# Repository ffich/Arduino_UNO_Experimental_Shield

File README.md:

# Arduino_UNO_Experimental_Shield
Experimental shield for Arduino UNO form factor boards.

Welcome to the official repository of the **UNO Experimental SHIELD**, an expansion board designed to provide a complete laboratory environment for experimenting, testing, and learning with the Arduino UNO Boards (e.g **UNO Q**).
This shield integrates digital and analog I/O, SPI, I2C, sensors, memory, and diagnostics to create a versatile platform ideal for rapid prototyping, debugging, and education.

---

## 🚀 Key Features

### 🔹 Digital I/O
- SMD LEDs on pins **D2, D3, D6, D7, D8, D9**
- Push buttons on pins **A2, A3**

### 🔹 Analog Inputs
- **Two 100 kΩ trimmers** on analog inputs **A0, A1**  

### 🔹 Serial Communication
- **USB-to-Serial bridge** (CH340)  

### 🔹 CAN Bus
- **CAN transceiver** (TJA1051T3)  
- **120 Ω termination resistor** enabled by jumper  
- Screw terminal output: CANH / CANL

### 🔹 RS-485
- **RS485 transceiver**
- **120 Ω termination resistor** enabled by jumper  
- Screw terminal output: A / B 

### 🔹 I2C Display
- Integrated **SSD1306 OLED display**

### 🔹 I2C Thermometer
- Integrated **TMP102 thermo**  

### 🔹 SPI Memory
- **25LC256 EEPROM** connected to hardware SPI  
- Dedicated Chip Select line

### 🔹 Crypto Chip
- Integrated **ATECC608C**  - 

---

## 📐 Pinout Summary

### Digital I/O
| UNO Pin | Shield Function |
|------------|-----------------|
| D2, D3, D6, D7, D8, D9 | LED  |
| A2, A3 | Buttons  |

### Analog
| Pin | Function |
|-----|----------|
| A0 | Trimmer 1 |
| A1 | Trimmer 2 |

### Peripherals
| Function | Pin |
|----------|-----|
| SPI EEPROM | MOSI / MISO / SCK + CS |
| I2C OLED | SDA / SCL |
| I2C Thermo | SDA / SCL |
| I2C Crypto Chip | SDA / SCL |
| CAN | CAN_TX / CAN_RX |
| RS485 | TX / RX |
| USB-Serial | TX / RX |

The Shield is compatible with both Arduino UNOs with 3V3 and 5V logic (some jumpers allow to adapt the voltage levels).

---

## 🛠️ Project Goals

This shield is intended for:
- Users who want a **complete test environment** for Arduino UNO Boards (e.g. **UNO Q**, **UNO R4**) 
- Makers performing **rapid firmware debugging**  
- Schools, workshops, and educational labs  
- Testing all core firmware interfaces (PWM, ADC, SPI, I2C, CAN, UART)

---

## 📷 Logo

The official project logo is available in the `/assets/logo/` directory.

---

## 📝 License

This project is released under the **MIT License**, unless otherwise specified for hardware files.

---

## 🤝 Contributing

Pull requests and issues are welcome!  
Contributions improving documentation, firmware examples, or hardware design are highly appreciated.

---

## 📫 Contact

For questions or suggestions, open an Issue in the repository or contact the maintainer.

---

Happy experimenting! 🔧✨

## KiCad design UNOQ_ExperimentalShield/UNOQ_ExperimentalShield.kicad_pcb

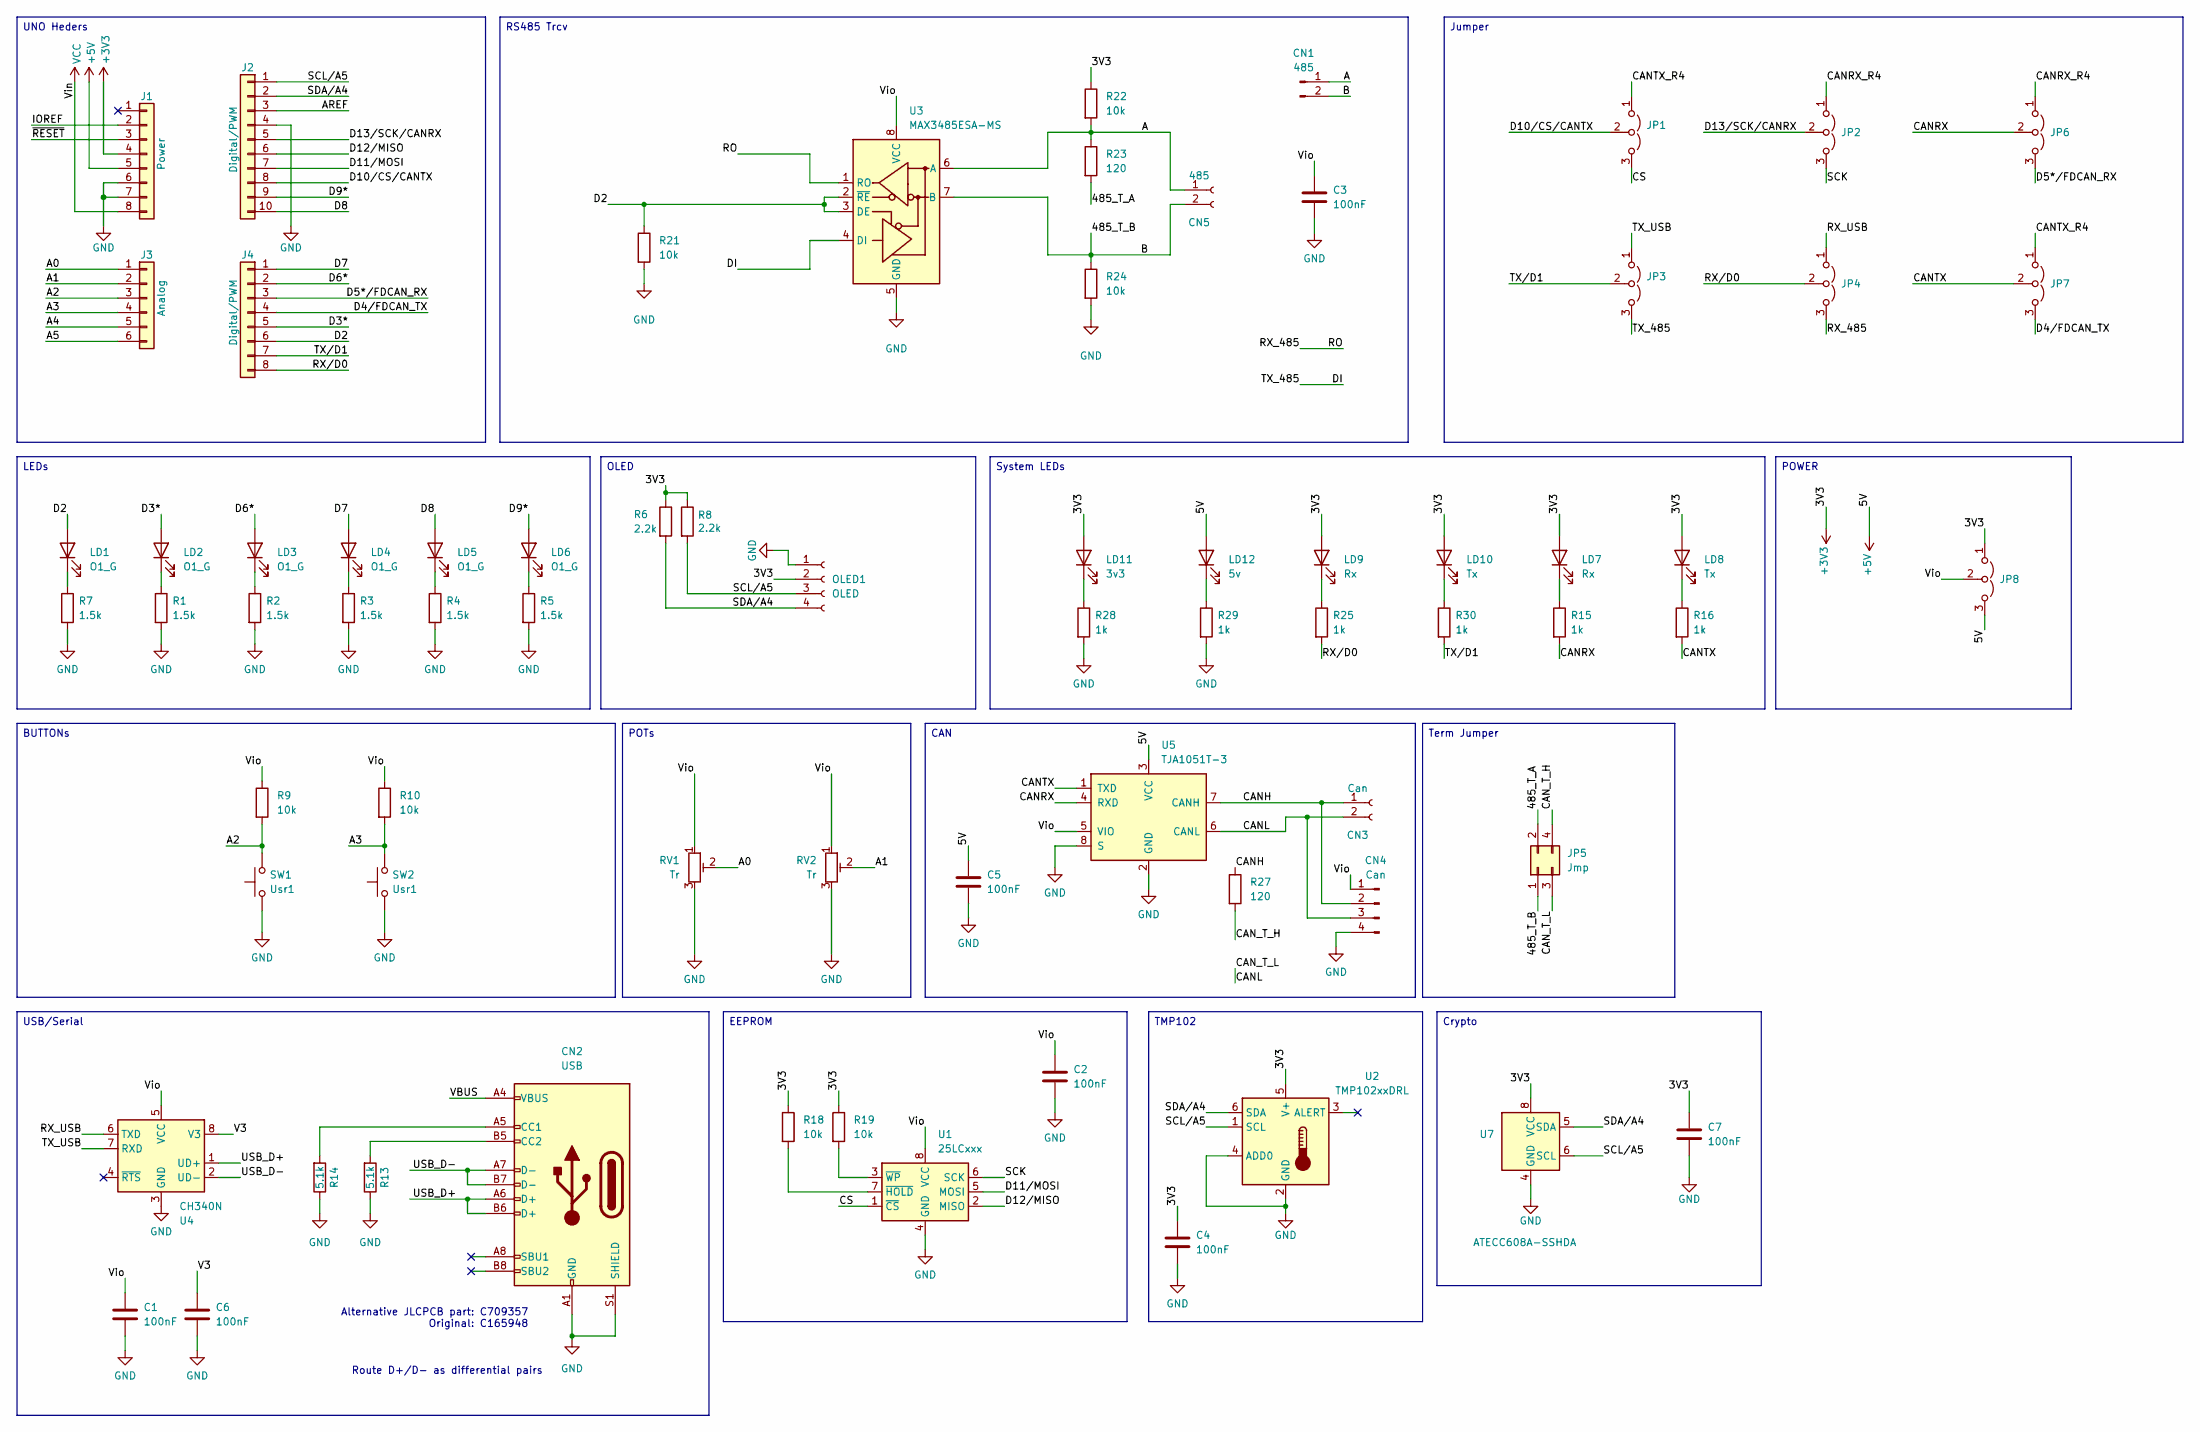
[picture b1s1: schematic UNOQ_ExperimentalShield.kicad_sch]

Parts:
C1, C2, C3, C4, C5, C6, C7: 100nF; C_0402_1005Metric; LCSC C155422
CN1: 485; PinHeader_1x02_P2.54mm_Vertical; LCSC C5360898
CN2: USB; USB_C_Receptacle_HRO_TYPE-C-31-M-12; LCSC C165948
CN3: Can; TerminalBlock_Phoenix_MPT-0,5-2-2.54_1x02_P2.54mm_Horizontal; LCSC C474920
CN4: Can; PinHeader_1x04_P2.54mm_Vertical; LCSC C2905435
CN5: 485; TerminalBlock_Phoenix_MPT-0,5-2-2.54_1x02_P2.54mm_Horizontal; LCSC C474920
J1: Power; PinHeader_1x08_P2.54mm_Vertical; LCSC C32713274
J2: Digital/PWM; PinHeader_1x10_P2.54mm_Vertical; LCSC C57369
J3: Analog; PinHeader_1x06_P2.54mm_Vertical; LCSC C32713272
J4: Digital/PWM; PinHeader_1x08_P2.54mm_Vertical; LCSC C32713274
JP1, JP2, JP3, JP4, JP6, JP7, JP8: Jmp; PinHeader_1x03_P2.54mm_Vertical; LCSC C49257
JP5: Jmp; PinHeader_2x02_P2.54mm_Vertical; LCSC C32713275
LD1, LD2, LD3, LD4, LD5, LD6: O1_G; LED_0603_1608Metric; LCSC C12624
LD7, LD9: Rx; LED_0603_1608Metric; LCSC C2286
LD8, LD10: Tx; LED_0603_1608Metric; LCSC C2286
LD11: 3v3; LED_0603_1608Metric; LCSC C2286
LD12: 5v; LED_0603_1608Metric; LCSC C2286
OLED1: OLED; OLED096; LCSC C5248080
R1, R2, R3, R4, R5, R7: 1.5k; R_0402_1005Metric; LCSC C25867
R6, R8: 2.2k; R_0603_1608Metric
R9, R10, R18, R19, R21, R22, R24: 10k; R_0402_1005Metric; LCSC C174175
R13, R14: 5.1k; R_0402_1005Metric; LCSC C25905
R15, R16, R25, R28, R29, R30: 1k; R_0402_1005Metric; LCSC C140196
R23, R27: 120; R_0603_1608Metric; LCSC C177328
RV1, RV2: Tr; Potentiometer_Bourns_3386P_Vertical; LCSC C116303
SW1, SW2: Usr1; SW_SPST_PTS810; LCSC C221895
U1: 25LCxxx; SO-8_3.9x4.9mm_P1.27mm; LCSC C84670
U2: TMP102xxDRL; SOT-563; LCSC C99269
U3: MAX3485ESA-MS; SOIC-8_3.9x4.9mm_P1.27mm; LCSC C7434431
U4: CH340N; JEITA_SOIC-8_3.9x4.9mm_P1.27mm; LCSC C2977777
U5: TJA1051T-3; SOIC-8_3.9x4.9mm_P1.27mm; LCSC C38695
U7: ATECC608A-SSHDA; SOIC-8_3.9x4.9mm_P1.27mm; LCSC C28975195

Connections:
+3V3: C4.1, C7.1, J1.4, JP8.1 (A), LD7.2 (A), LD8.2 (A), LD9.2 (A), LD10.2 (A), LD11.2 (A), OLED1.2, R6.1, R8.1, R18.1, R19.1, R22.1, U2.5 (V+), U7.8 (VCC)
+5V: C5.1, J1.5, JP8.3 (B), LD12.2 (A), U5.3 (VCC)
/485_T_A: JP5.2, R23.2
/485_T_B: CN1.2, CN5.2, JP5.1, R24.1, U3.7 (B)
/A: CN1.1, CN5.1, R22.2, R23.1, U3.6 (A)
/A0: J3.1, RV1.2
/A1: J3.2, RV2.2
/A2: J3.3, R9.2, SW1.2
/A3: J3.4, R10.2, SW2.2
/A4: J3.5
/A5: J3.6
/AREF: J2.3
/CANH: CN3.1, CN4.2, R27.1, U5.7 (CANH)
/CANL: CN3.2, CN4.3, JP5.3, U5.6 (CANL)
/CANRX: JP6.2 (C), R15.2, U5.4 (RXD)
/CANRX_R4: JP2.1 (A), JP6.1 (A)
/CANTX: JP7.2 (C), R16.2, U5.1 (TXD)
/CANTX_R4: JP1.1 (A), JP7.1 (A)
/CAN_T_H: JP5.4, R27.2
/CS: JP1.3 (B), U1.1 (~CS)
/D2: J4.6, LD1.2 (A), R21.1, U3.2 (~RE), U3.3 (DE)
/D3*: J4.5, LD2.2 (A)
/D4/FDCAN_TX: J4.4, JP7.3 (B)
/D5*/FDCAN_RX: J4.3, JP6.3 (B)
/D6*: J4.2, LD3.2 (A)
/D7: J4.1, LD4.2 (A)
/D8: J2.10, LD5.2 (A)
/D9*: J2.9, LD6.2 (A)
/D10/CS/CANTX: J2.8, JP1.2 (C)
/D11/MOSI: J2.7, U1.5 (MOSI)
/D12/MISO: J2.6, U1.2 (MISO)
/D13/SCK/CANRX: J2.5, JP2.2 (C)
/DI: JP3.3 (B), U3.4 (DI)
/IOREF: J1.2
/RO: JP4.3 (B), U3.1 (RO)
/RX_USB: JP4.1 (A), U4.6 (TXD)
/RX/D0: J4.8, JP4.2 (C), R25.2
/SCK: JP2.3 (B), U1.6 (SCK)
/SCL/A5: J2.1, OLED1.3, R8.2, U2.1 (SCL), U7.6 (SCL)
/SDA/A4: J2.2, OLED1.4, R6.2, U2.6 (SDA), U7.5 (SDA)
/TX_USB: JP3.1 (A), U4.7 (RXD)
/TX/D1: J4.7, JP3.2 (C), R30.2
/USB_D+: CN2.A6 (D+), CN2.B6 (D+), U4.1 (UD+)
/USB_D-: CN2.A7 (D-), CN2.B7 (D-), U4.2 (UD-)
/V3: C6.1, U4.8 (V3)
/VBUS: CN2.A4 (VBUS), CN2.A9 (VBUS), CN2.B4 (VBUS), CN2.B9 (VBUS)
/Vio: C1.1, C2.1, C3.1, CN4.1, JP8.2 (C), R9.1, R10.1, RV1.1, RV2.1, U1.8 (VCC), U3.8 (VCC), U4.5 (VCC), U5.5 (VIO)
/~RESET: J1.3
GND: C1.2, C2.2, C3.2, C4.2, C5.2, C6.2, C7.2, CN2.A1 (GND), CN2.A12 (GND), CN2.B1 (GND), CN2.B12 (GND), CN2.S1 (SHIELD), CN4.4, J1.6, J1.7, J2.4, OLED1.1, R1.2, R2.2, R3.2, R4.2, R5.2, R7.2, R13.1, R14.1, R21.2, R24.2, R28.2, R29.2, RV1.3, RV2.3, SW1.1, SW2.1, U1.4 (GND), U2.2 (GND), U2.4 (ADD0), U3.5 (GND), U4.3 (GND), U5.2 (GND), U5.8 (S), U7.4 (GND)
unnamed: CN2.A5 (CC1), R14.2
unnamed: CN2.B5 (CC2), R13.2
unnamed: LD1.1 (K), R7.1
unnamed: LD2.1 (K), R1.1
unnamed: LD3.1 (K), R2.1
unnamed: LD4.1 (K), R3.1
unnamed: LD5.1 (K), R4.1
unnamed: LD6.1 (K), R5.1
unnamed: LD7.1 (K), R15.1
unnamed: LD8.1 (K), R16.1
unnamed: LD9.1 (K), R25.1
unnamed: LD10.1 (K), R30.1
unnamed: LD11.1 (K), R28.1
unnamed: LD12.1 (K), R29.1
unnamed: R18.2, U1.7 (~HOLD)
unnamed: R19.2, U1.3 (~WP)
VCC: J1.8

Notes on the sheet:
Route D+/D- as differential pairs
Alternative JLCPCB part: C709357 Original: C165948
System LEDs
LEDs
TMP102
Term Jumper
CAN
OLED
EEPROM
Crypto
RS485 Trcv
Jumper
POTs
POWER
UNO Heders
USB/Serial
BUTTONs

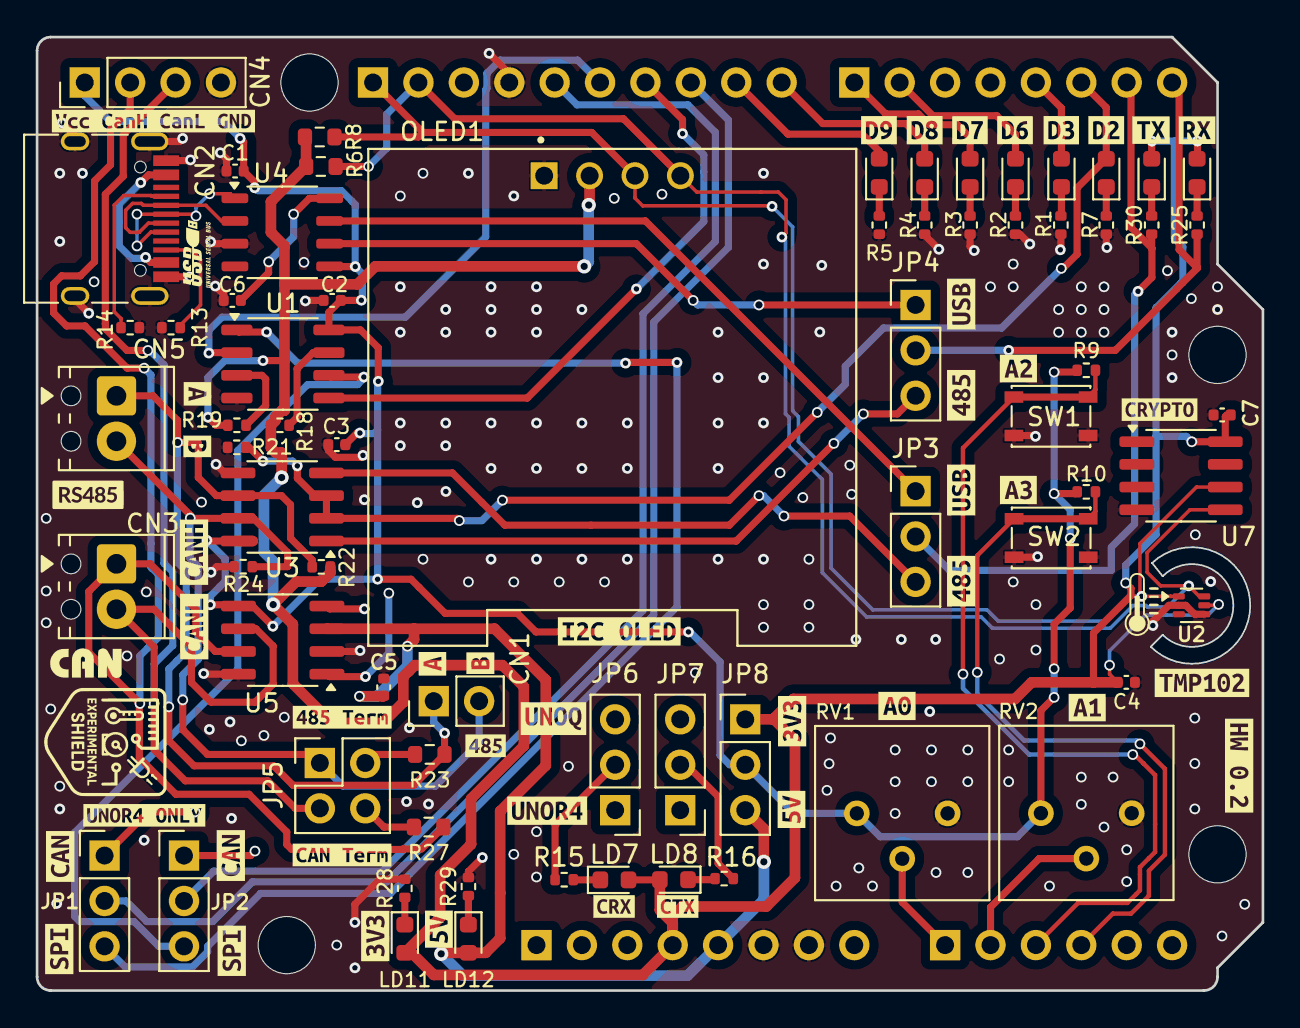
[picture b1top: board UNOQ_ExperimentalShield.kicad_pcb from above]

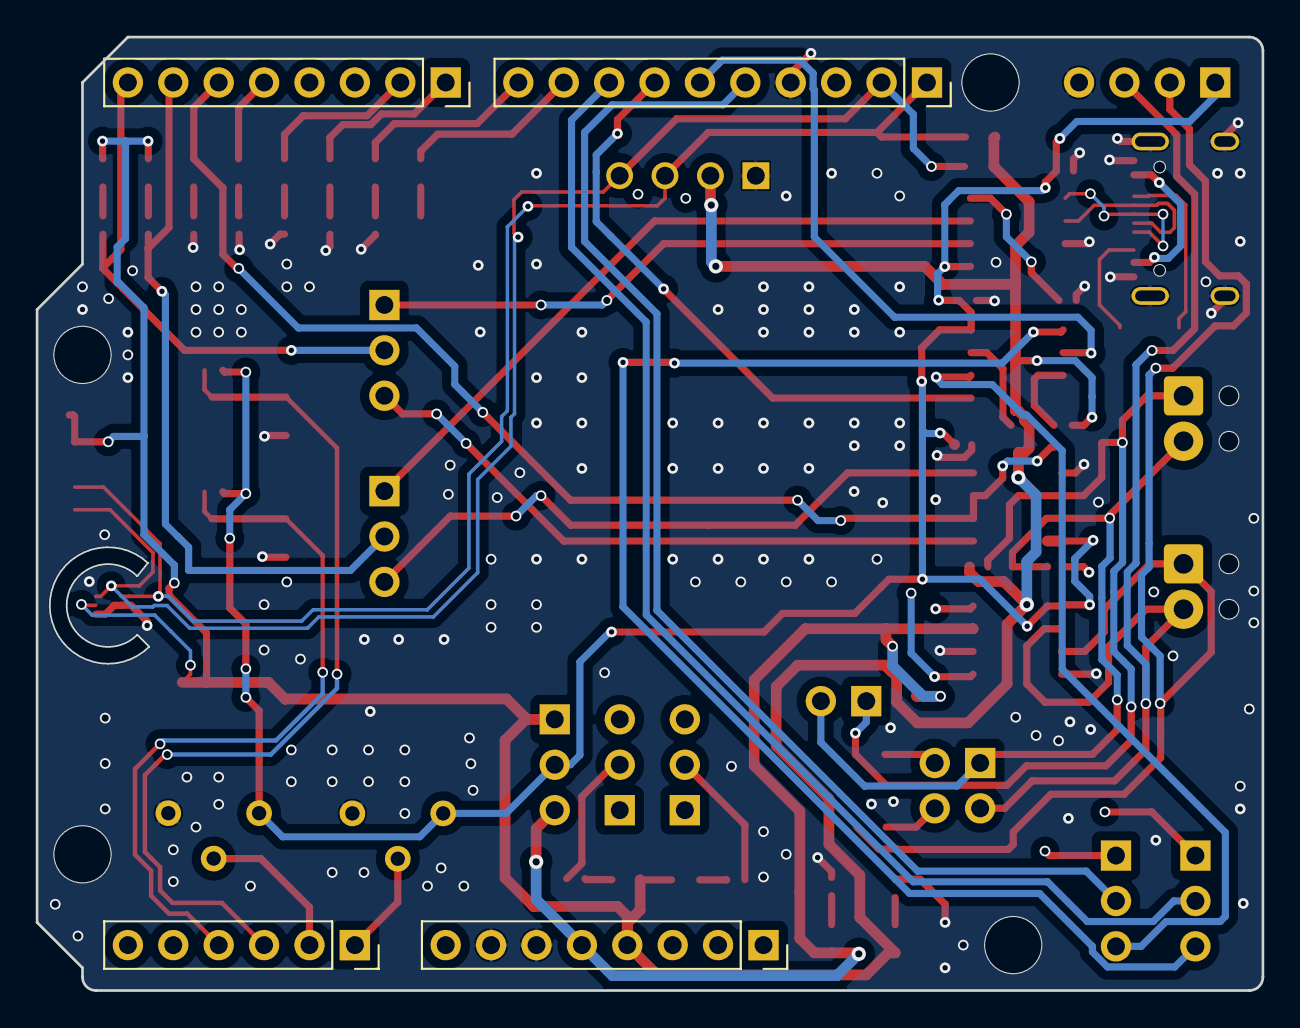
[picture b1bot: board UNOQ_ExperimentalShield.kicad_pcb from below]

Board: 4 copper layers, 68.6 x 53.3 mm, 119 parts (4 on the bottom side), 60 nets.

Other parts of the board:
MH1, MH2, MH3, MH4: MountingHole_3.2mm
kibuzzard-69DFD334: G***; kibuzzard-69DFD334
kibuzzard-69E2216E: G***; kibuzzard-69E2216E
kibuzzard-69E22173: G***; kibuzzard-69E22173
kibuzzard-69E66319: G***; kibuzzard-69E66319
kibuzzard-69ECB5A8: G***; kibuzzard-69ECB5A8
kibuzzard-69ECB57B: G***; kibuzzard-69ECB57B
kibuzzard-69ECB59B: G***; kibuzzard-69ECB59B
kibuzzard-69ECB574: G***; kibuzzard-69ECB574
kibuzzard-693AADEF: G***; kibuzzard-693AADEF
kibuzzard-697C8D0C: G***; kibuzzard-697C8D0C
kibuzzard-697C8D01: G***; kibuzzard-697C8D01
kibuzzard-697C896A: G***; kibuzzard-697C896A
kibuzzard-697C897C: G***; kibuzzard-697C897C
kibuzzard-697C8970: G***; kibuzzard-697C8970
kibuzzard-697C8977: G***; kibuzzard-697C8977
kibuzzard-69443E7E: G***; kibuzzard-69443E7E
kibuzzard-69443E38: G***; kibuzzard-69443E38
kibuzzard-69443E67: G***; kibuzzard-69443E67
kibuzzard-69595BB4: G***; kibuzzard-69595BB4
kibuzzard-69595BC0: G***; kibuzzard-69595BC0
kibuzzard-69595C5E: G***; kibuzzard-69595C5E
kibuzzard-69595C8D: G***; kibuzzard-69595C8D
kibuzzard-69595C64: G***; kibuzzard-69595C64
kibuzzard-69595C77: G***; kibuzzard-69595C77
kibuzzard-69595C82: G***; kibuzzard-69595C82
kibuzzard-69595C87: G***; kibuzzard-69595C87
kibuzzard-69595C92: G***; kibuzzard-69595C92
kibuzzard-69595C98: G***; kibuzzard-69595C98
kibuzzard-69595CA1: G***; kibuzzard-69595CA1
kibuzzard-69595CF0: G***; kibuzzard-69595CF0
kibuzzard-69595CF5: G***; kibuzzard-69595CF5
kibuzzard-69595D7B: G***; kibuzzard-69595D7B
kibuzzard-69595D77: G***; kibuzzard-69595D77
kibuzzard-69595D81: G***; kibuzzard-69595D81
kibuzzard-69764F79: G***; kibuzzard-69764F79
kibuzzard-69878B44: G***; kibuzzard-69878B44
kibuzzard-698784C3: G***; kibuzzard-698784C3
kibuzzard-698784D4: G***; kibuzzard-698784D4
kibuzzard-6976550D: G***; kibuzzard-6976550D
kibuzzard-6987886F: G***; kibuzzard-6987886F
kibuzzard-6987894B: G***; kibuzzard-6987894B
kibuzzard-69765506: G***; kibuzzard-69765506
kibuzzard-69878868: G***; kibuzzard-69878868

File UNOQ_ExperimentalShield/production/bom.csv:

Designator,Footprint,Quantity,Value,LCSC Part #
"C1, C2, C3, C4, C5, C6, C7",0402,7,100nF,C155422
CN1,PinHeader_1x02_P2.54mm_Vertical,1,485,C5360898
CN2,USB_C_Receptacle_HRO_TYPE-C-31-M-12,1,USB,C165948
CN3,"TerminalBlock_Phoenix_MPT-0,5-2-2.54_1x02_P2.54mm_Horizontal",1,Can,C474920
CN4,PinHeader_1x04_P2.54mm_Vertical,1,Can,C2905435
CN5,"TerminalBlock_Phoenix_MPT-0,5-2-2.54_1x02_P2.54mm_Horizontal",1,485,C474920
"JP1, JP2, JP3, JP4, JP6, JP7, JP8",PinHeader_1x03_P2.54mm_Vertical,7,Jmp,C49257
JP5,PinHeader_2x02_P2.54mm_Vertical,1,Jmp,C32713275
"LD1, LD2, LD3, LD4, LD5, LD6",0603,6,O1_G,C12624
"LD10, LD8",0603,2,Tx,C2286
LD11,0603,1,3v3,C2286
LD12,0603,1,5v,C2286
"LD7, LD9",0603,2,Rx,C2286
OLED1,OLED096,1,OLED,C5248080
"R1, R2, R3, R4, R5, R7",0402,6,1.5k,C25867
"R10, R18, R19, R21, R22, R24, R9",0402,7,10k,C174175
"R13, R14",0402,2,5.1k,C25905
"R15, R16, R25, R28, R29, R30",0402,6,1k,C140196
"R23, R27",0603,2,120,C177328
"R6, R8",0603,2,2.2k,
"RV1, RV2",Potentiometer_Bourns_3386P_Vertical,2,Tr,C116303
"SW1, SW2",SW_SPST_PTS810,2,Usr1,C221895
U1,SO-8_3.9x4.9mm_P1.27mm,1,25LCxxx,C84670
U2,SOT-563,1,TMP102xxDRL,C99269
U3,SOIC-8_3.9x4.9mm_P1.27mm,1,MAX3485ESA-MS,C7434431
U4,JEITA_SOIC-8_3.9x4.9mm_P1.27mm,1,CH340N,C2977777
U5,SOIC-8_3.9x4.9mm_P1.27mm,1,TJA1051T-3,C38695
U7,SOIC-8_3.9x4.9mm_P1.27mm,1,ATECC608A-SSHDA,C28975195

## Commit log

2025-12-11 Added board project.
2025-12-11 Updated description
2025-12-11 Update README.md
    updated
2025-12-12 added sch and ibom
2025-12-17 minor
2026-01-08 Some fixes: - Fixed labesl dimension - Fixed resistor values for leds - Fixed OLED footprint - Added HW version
2026-01-25 Some modifications: - TX/RX Led polarity inverted - LM35 has been replaced with TMP102 (I2C Thermo, better and cheaper) - OLED Shape has been fixed - LED Resistors updated to 1k
2026-02-08 final vesion
2026-02-08 Update README.md
    Updated description
2026-04-21 List of changes/fixes: - Buttons reducto 2 and moved to A2, A3 - Fixed TX/RX CAN lines for R4 - Buttons tied to Vio - Pots tied to Vio - Added ATECC608 secure element
2026-04-21 Added R4 test sketch
2026-04-25 Added unoq (without can) test sketch
2026-04-25 Rename Secure Element to Crypto Chip in README
2026-04-25 Some updates
